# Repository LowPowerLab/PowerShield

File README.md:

PowerShield
===========

## Power Shield source files
Details and specs at: http://www.lowpowerlab.com/powershield

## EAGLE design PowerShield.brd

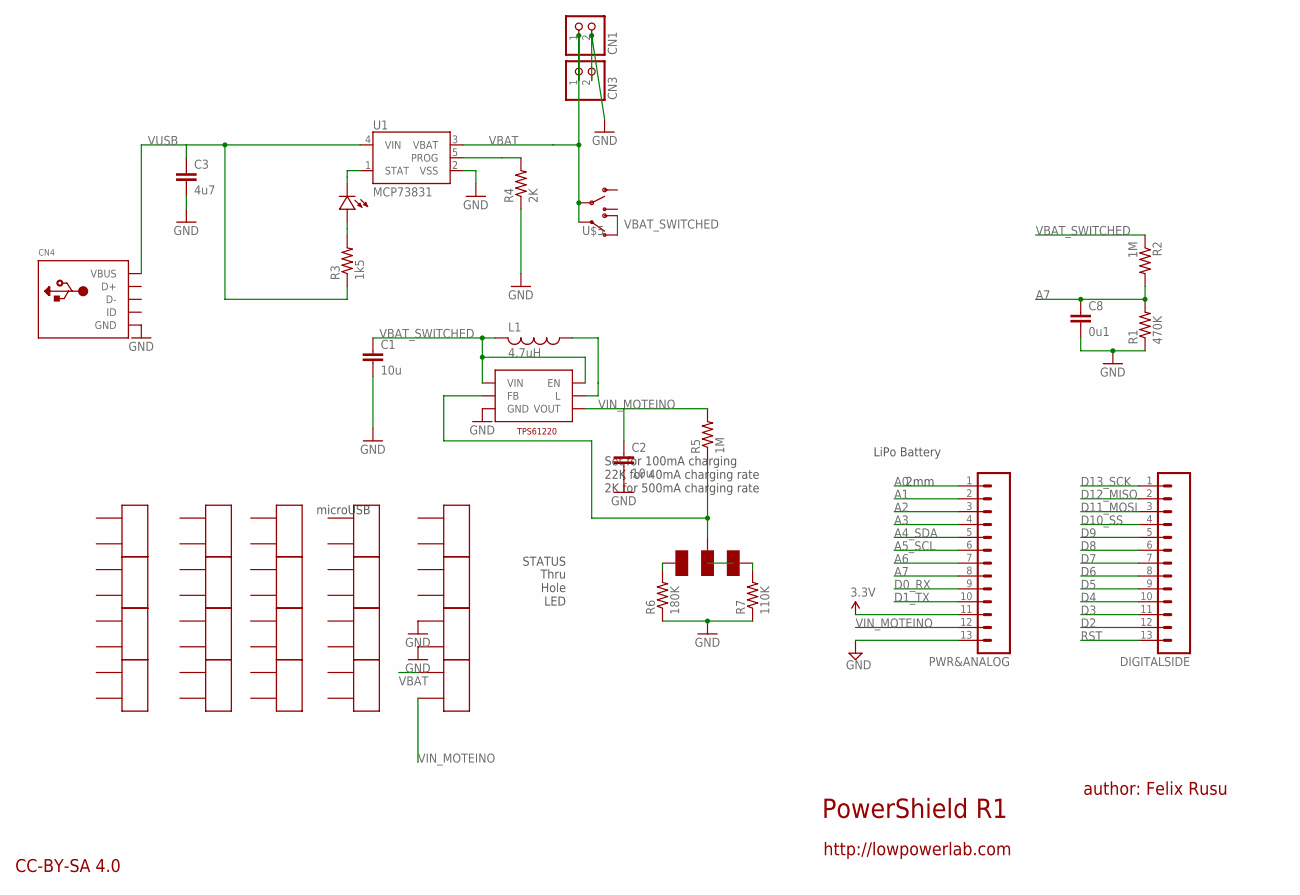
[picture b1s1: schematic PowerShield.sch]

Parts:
C1, C2: 10u; 0805-CAP-LARGEPADS
C3: 4u7; 0603-CAP
C8: 0u1; 0603-CAP
CN1: JST_2PIN-THM-RA; JST-PH-2-THM-RA
CN3: JST_2PIN-SMT-RA; JST-PH-2-SMT-RA
CN4: USBMINIB; USB-MINIB
DIGITALSIDE: HDR_13PINREGULAR; 1X13
L1: 4.7uH; INDUCTOR_NR3015
PWR&ANALOG: HDR_13PINREGULAR; 1X13
R1: 470K; 0603-RES
R2, R5: 1M; 0603-RES
R3: 1k5; 0603-RES
R4: 2K; 0603-RES
R6: 180K; 0603-RES
R7: 110K; 0603-RES
U1: MCP73831; SOT23-5
U$1: SWITCH_SPDT; SWITCH-SPDT
U$2: TPS61222SOT363; SOT363
U$4: LED0603; 0603-LED
U$5: SWITCH_SPDT; KPS-1290
U$6, U$7, U$8, U$9, U$10, U$11, U$12, U$13, U$14, U$15, U$16, U$17, U$18, U$19, U$20, U$21, U$22, U$23, U$24, U$25: HDR_2PIN; 1X02_NS
U$26: JUMPER_3

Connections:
A0: PWR&ANALOG.1
A1: PWR&ANALOG.2
A2: PWR&ANALOG.3
A3: PWR&ANALOG.4
A4_SDA: PWR&ANALOG.5
A5_SCL: PWR&ANALOG.6
A6: PWR&ANALOG.7
A7: C8.1, PWR&ANALOG.8, R1.2, R2.2
D0_RX: PWR&ANALOG.9
D1_TX: PWR&ANALOG.10
D2: DIGITALSIDE.12
D3: DIGITALSIDE.11
D4: DIGITALSIDE.10
D5: DIGITALSIDE.9
D6: DIGITALSIDE.8
D7: DIGITALSIDE.7
D8: DIGITALSIDE.6
D9: DIGITALSIDE.5
D10_SS: DIGITALSIDE.4
D11_MOSI: DIGITALSIDE.3
D12_MISO: DIGITALSIDE.2
D13_SCK: DIGITALSIDE.1
GND: C1.2, C2.2, C3.2, C8.2, CN1.2 (1), CN3.2 (1), CN4.GND, PWR&ANALOG.13, R1.1, R4.1, R6.1, R7.1, U1.2 (VSS), U$2.3 (GND), U$24.1, U$24.2
unnamed: L1.P$1 (1), U$2.5 (L)
unnamed: R3.2, U$4.PLUS
unnamed: R6.2, U$26.3
unnamed: R7.2, U$26.1
unnamed: R5.1, U$2.2 (FB), U$26.2
PROG: R4.2, U1.5 (PROG)
RST: DIGITALSIDE.13
STAT: U1.1 (STAT), U$4.MINUS
VBAT: CN1.1 (2), CN3.1 (2), U1.3 (VBAT), U$1.2, U$5.P, U$25.1
VBAT_SWITCHED: C1.1, L1.P$2 (2), R2.1, U$1.1, U$2.1 (VIN), U$2.6 (EN), U$5.S
VCC: PWR&ANALOG.11
VIN_MOTEINO: C2.1, PWR&ANALOG.12, R5.2, U$2.4 (VOUT), U$25.2
VUSB: C3.1, CN4.VBUS, R3.1, U1.4 (VIN)

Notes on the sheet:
PowerShield R1
author: Felix Rusu
http://lowpowerlab.com
Set for 100mA charging 22K for 40mA charging rate 2K for 500mA charging rate
LiPo Battery
2mm
microUSB
Thru Hole LED
STATUS
CC-BY-SA 4.0
TPS61220

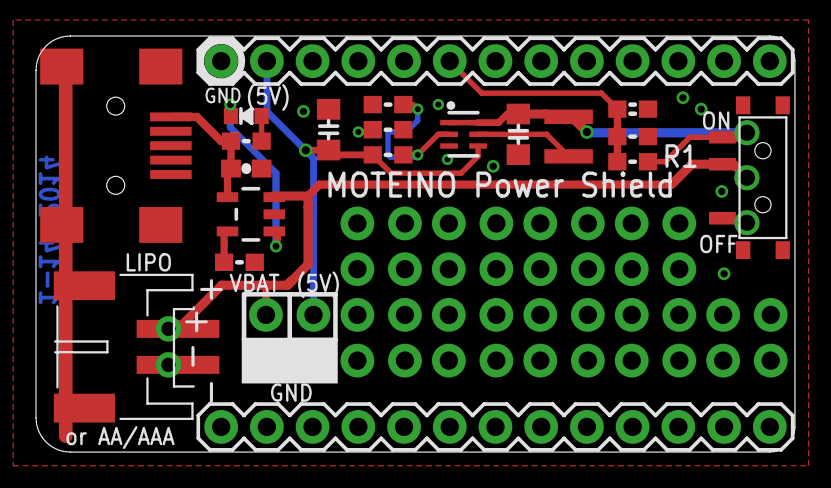
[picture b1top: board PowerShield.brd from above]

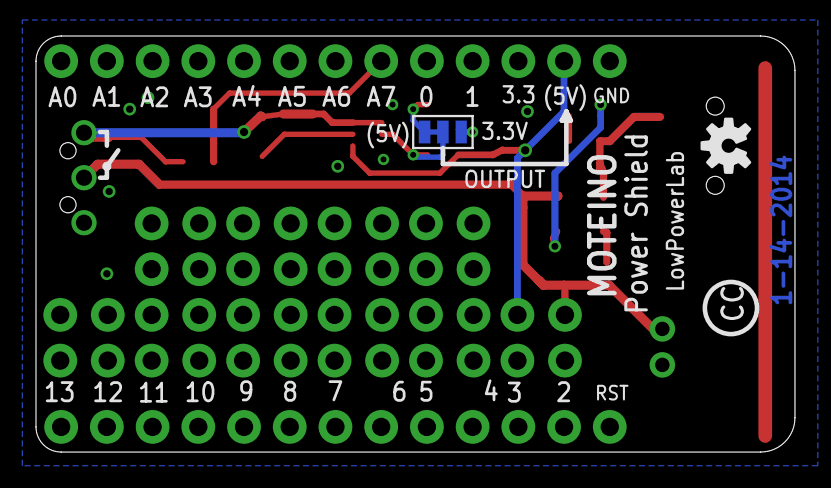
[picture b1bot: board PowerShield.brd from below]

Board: 2 copper layers, 42.2 x 23.1 mm, 44 parts (2 on the bottom side), 13 nets.

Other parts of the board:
U$3: OSHW-LOGO-S

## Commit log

2014-03-25 Add PDF format
2014-06-08 Add Rev2 files

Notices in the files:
parts and their libraries:
SparkFun-Aesthetics: Licensing: CC v3.0 Share-Alike You are welcome to use this library for commercial purposes.
